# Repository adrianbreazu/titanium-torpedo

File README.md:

# About

IoT Django project for Raspberry Pi 3. It uses a wide range of sensors and actuators. It also provides the PCB schematics for the IoT boards so you can build them yourself.

# PCB design

IoT PCB design can be found in _titanium-torpedo/doc/EaglePCB_ directory. They represent my design (beginner level) any suggestion will be appreciated.

# Hardware needed

1. Raspberry Pi 3 (for better performance)
2. Relay's
3. DS18B20 temperature sensor (used due to accuracy of +/- 0.5)

# Software needed

* Clone this project
* Raspbian-jessie lite

# Installation

1. Cline this project

# Images

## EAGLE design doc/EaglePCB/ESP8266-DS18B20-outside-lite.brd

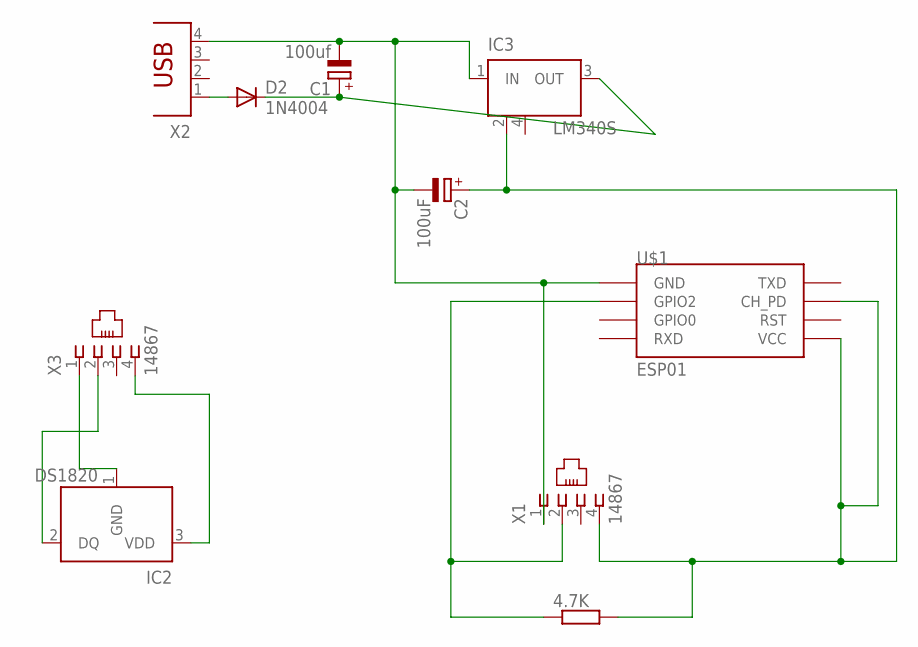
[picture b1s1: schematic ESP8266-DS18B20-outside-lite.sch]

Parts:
4.7K: SMK
C1: 100uf; E2,5-5
C2: 100uF; E2,5-5
D2: 1N4004; DO41-10
IC2: DS1820; TO-92
IC3: LM340S; SOT223
U$1: ESP01
X1, X3: 14867
X2: PN61729

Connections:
3V3: 4.7K.1, C2.+, IC3.2 (GND), U$1.CH_PD, U$1.VCC, X1.4; also elsewhere on the board
5V: C1.+, D2.A, D2.C, IC3.3 (OUT), X2.1
DQ: 4.7K.2, U$1.GPIO2, X1.2; also elsewhere on the board
GND: C1.-, C2.-, IC3.1 (IN), IC3.4 (GND), U$1.GND, X1.1, X2.4
P2_3V3: IC2.3 (VDD), X3.4
P2_DQ: IC2.2 (DQ), X3.2
P2_GND: IC2.1 (GND), X3.1

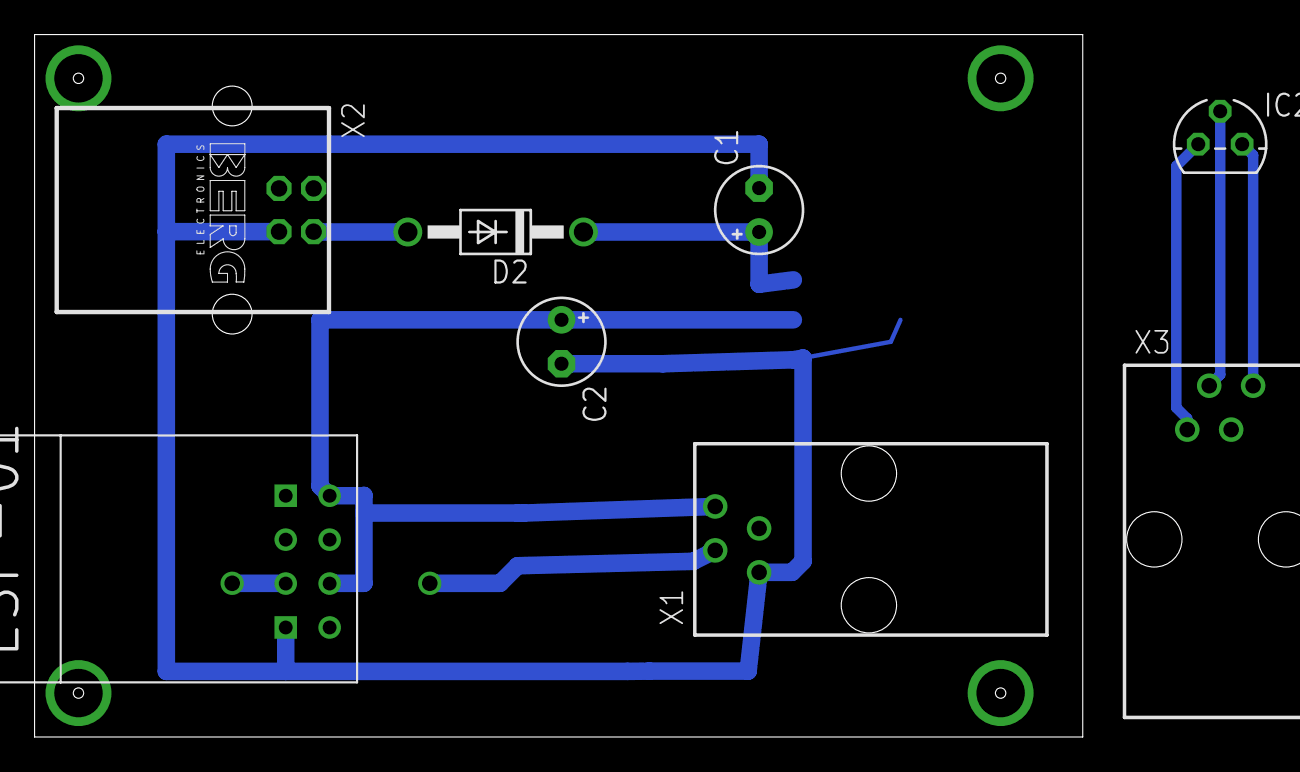
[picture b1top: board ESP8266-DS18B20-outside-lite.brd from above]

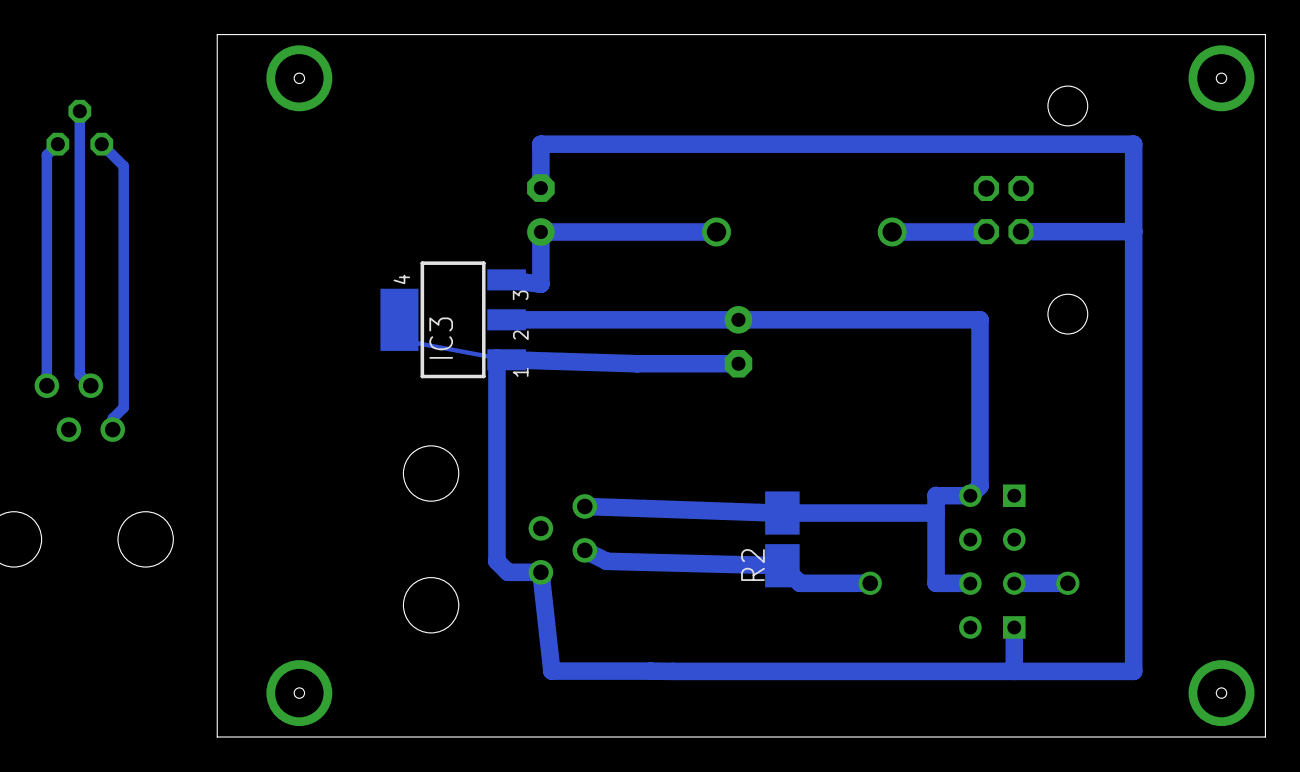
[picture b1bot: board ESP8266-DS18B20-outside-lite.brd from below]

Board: 2 copper layers, 60.6 x 40.6 mm, 10 parts (2 on the bottom side), 7 nets.

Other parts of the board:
R2: SMK

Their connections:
3V3: R2.1; also elsewhere on the board
DQ: R2.2; also elsewhere on the board

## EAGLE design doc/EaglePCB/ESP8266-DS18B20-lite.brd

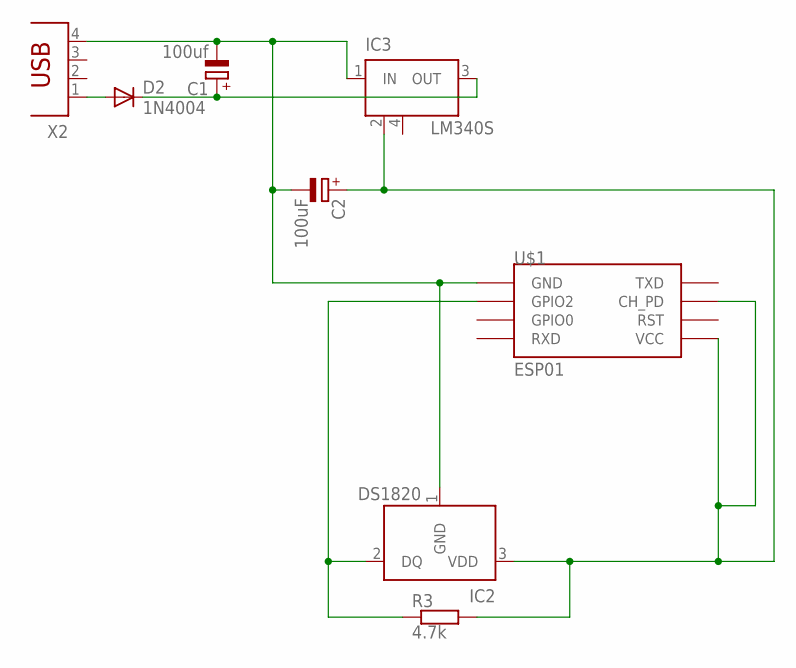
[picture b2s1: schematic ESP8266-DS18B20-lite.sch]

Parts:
C1: 100uf; E2,5-5
C2: 100uF; E2,5-5
D2: 1N4004; DO41-10
IC2: DS1820; TO-92
IC3: LM340S; SOT223
R3: 4.7k; SMK
U$1: ESP01
X2: PN61729

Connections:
3V3: C2.+, IC2.3 (VDD), IC3.2 (GND), R3.1, U$1.CH_PD, U$1.VCC
5V: C1.+, D2.A, D2.C, IC3.3 (OUT), X2.1
DQ: IC2.2 (DQ), R3.2, U$1.GPIO2
GND: C1.-, C2.-, IC2.1 (GND), IC3.1 (IN), IC3.4 (GND), U$1.GND, X2.4

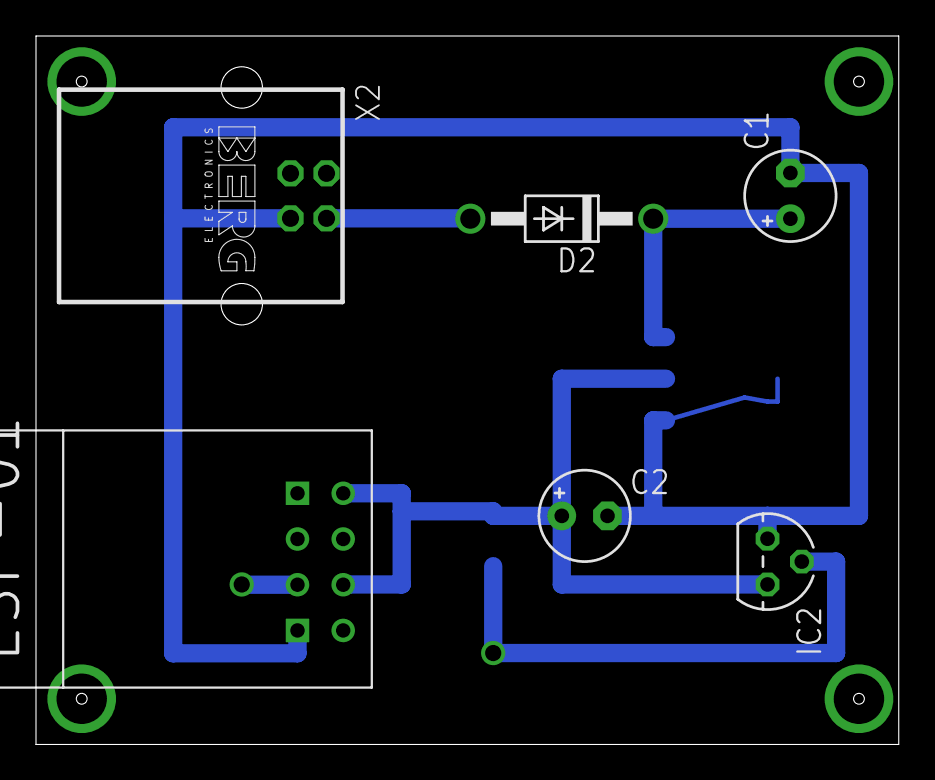
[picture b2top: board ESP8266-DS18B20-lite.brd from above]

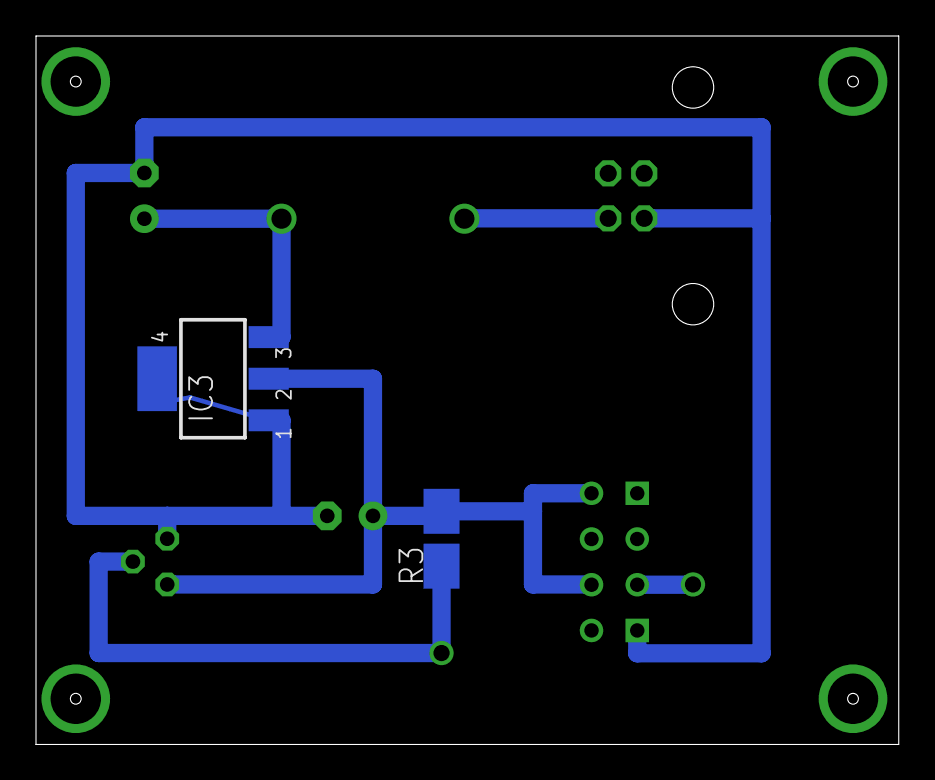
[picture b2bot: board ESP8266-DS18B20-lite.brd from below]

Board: 2 copper layers, 47.9 x 39.4 mm, 8 parts (2 on the bottom side), 4 nets.

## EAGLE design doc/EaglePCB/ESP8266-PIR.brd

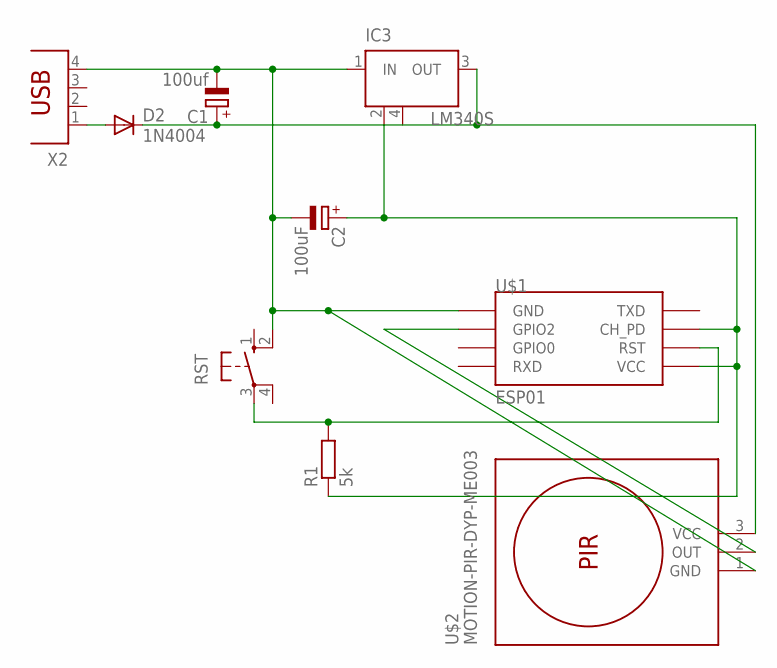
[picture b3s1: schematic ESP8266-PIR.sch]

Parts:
C1: 100uf; E2,5-5
C2: 100uF; E2,5-5
D2: 1N4004; DO41-10
IC3: LM340S; SOT223
R1: 5k; 0204/7
RST: 10-XX; B3F-10XX
U$1: ESP01
U$2: MOTION-PIR-DYP-ME003
X2: PN61729

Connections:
3V3: C2.+, IC3.2 (GND), R1.1, U$1.CH_PD, U$1.VCC
5V: C1.+, D2.A, D2.C, IC3.3 (OUT), U$2.3 (VCC), X2.1
GND: C1.-, C2.-, IC3.1 (IN), IC3.4 (GND), RST.2 (S1), U$1.GND, U$2.1 (GND), X2.4
GPIO2: U$1.GPIO2, U$2.2 (OUT)
unnamed: R1.2, RST.3, U$1.RST

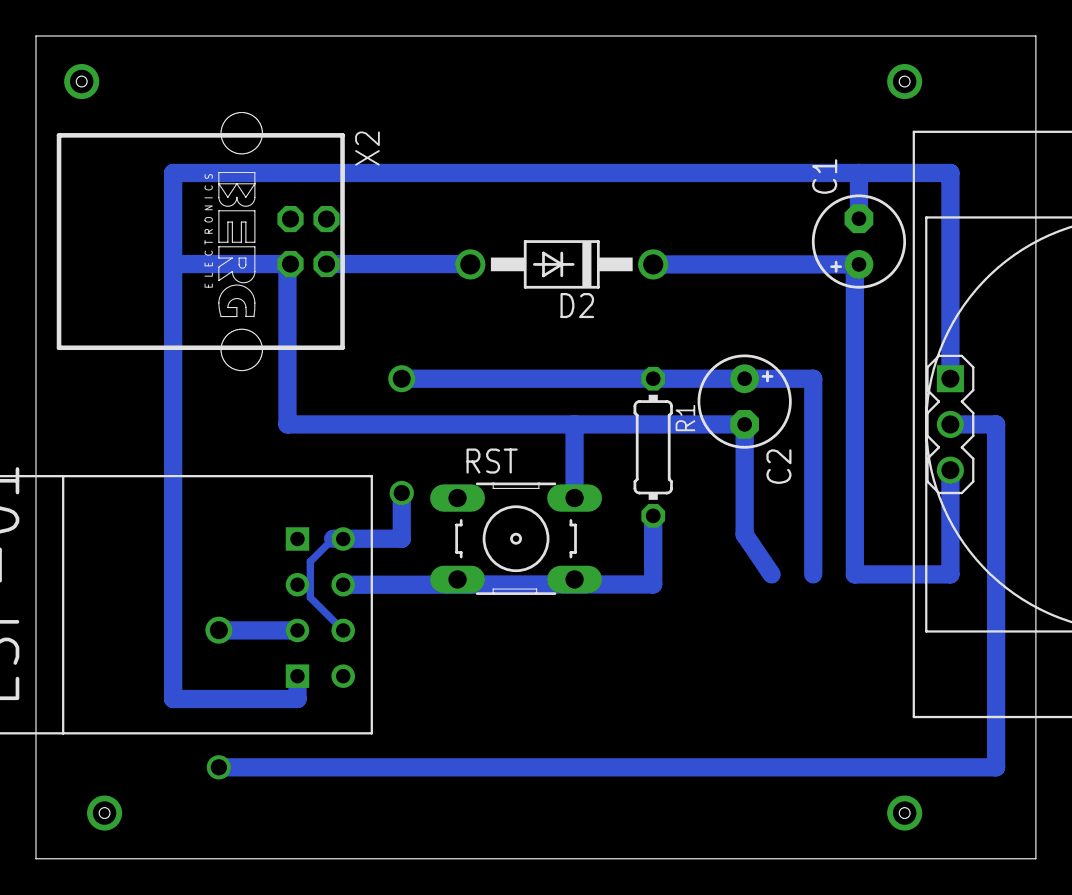
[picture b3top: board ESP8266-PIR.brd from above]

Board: 2 copper layers, 55.5 x 45.7 mm, 9 parts (1 on the bottom side), 5 nets.

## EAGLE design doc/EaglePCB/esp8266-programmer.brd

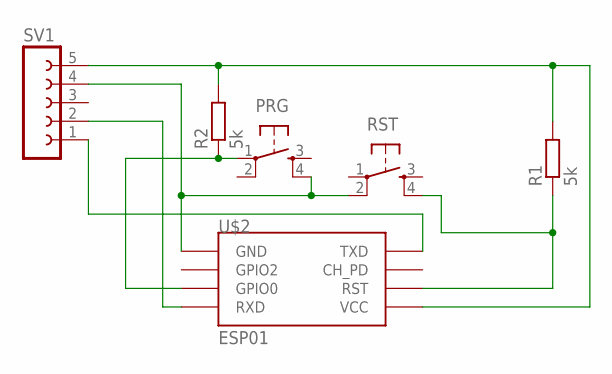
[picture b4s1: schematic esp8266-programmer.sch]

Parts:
PRG: TAC_SWITCHPTH; TACTILE-PTH
R1, R2: 5k; 0207/10
RST: TAC_SWITCHPTH; TACTILE-PTH
SV1: FE05W
U$2: ESP01

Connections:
3V3: R1.2, R2.2, SV1.5, U$2.VCC
GND: PRG.4, RST.2, SV1.4, U$2.GND
GPIO0: PRG.1, R2.1, U$2.GPIO0
RST: R1.1, RST.4, U$2.RST
RX-TX: SV1.1, U$2.TX (TXD)
TX-RX: SV1.2, U$2.RX (RXD)

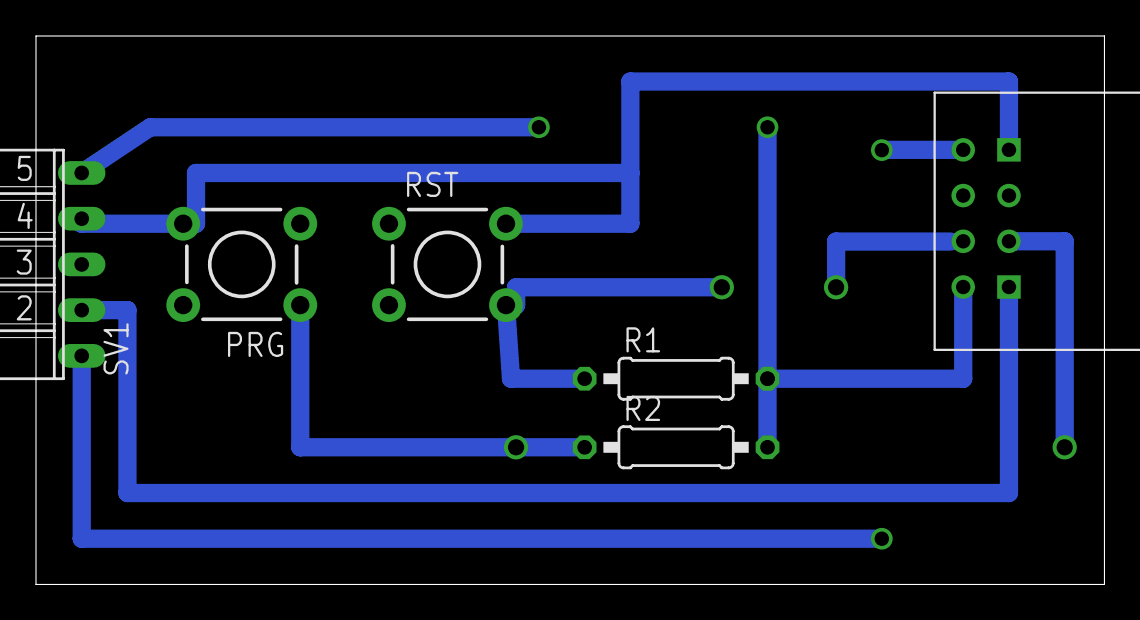
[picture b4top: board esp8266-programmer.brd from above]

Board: 2 copper layers, 59.4 x 30.5 mm, 6 parts (0 on the bottom side), 6 nets.

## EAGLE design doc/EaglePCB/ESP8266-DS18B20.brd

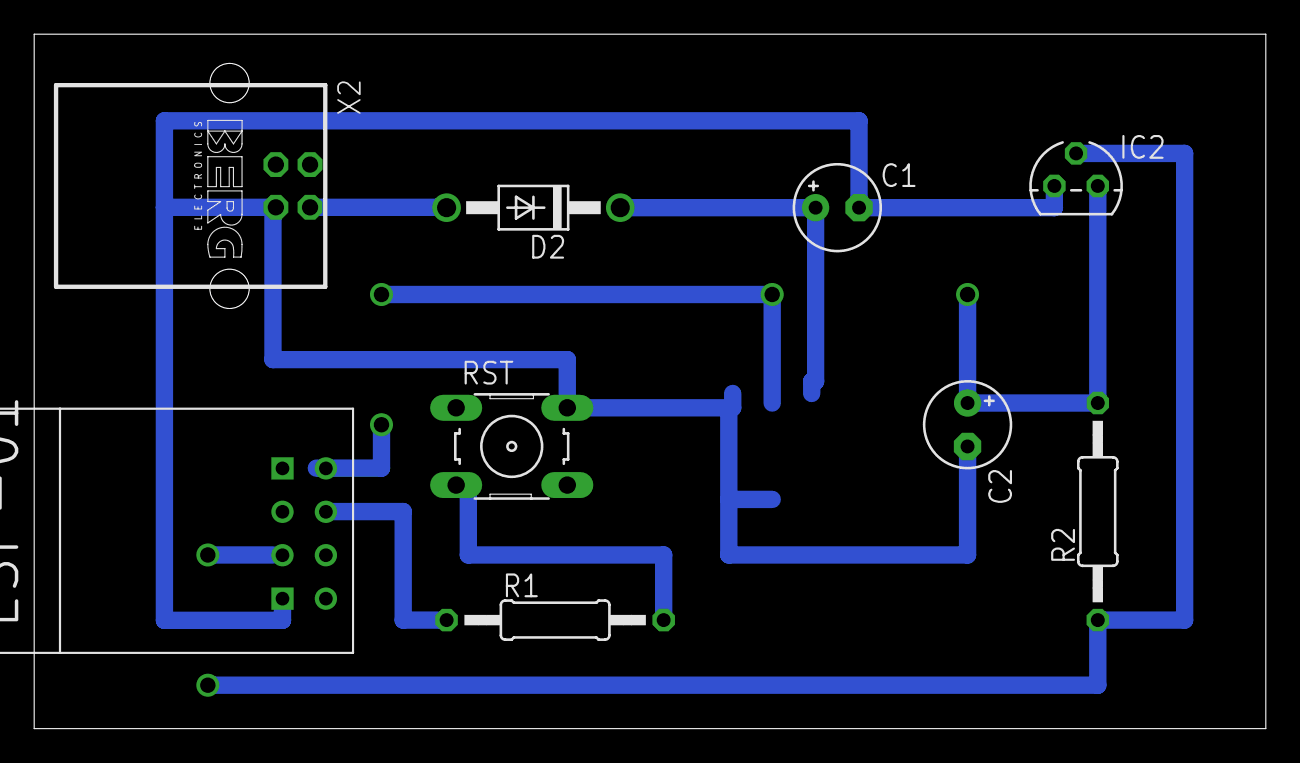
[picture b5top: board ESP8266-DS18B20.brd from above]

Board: 2 copper layers, 72.1 x 40.6 mm, 10 parts (1 on the bottom side), 6 nets.

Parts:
C1: 100uf; E2,5-5
C2: 100uF; E2,5-5
D2: 1N4004; DO41-10
IC2: DS1820; TO-92
IC3: LM340S; SOT223
R1: 1k; 0207/12
R2: 4.7k; 0207/12
RST: B3F-10XX
U$1: ESP01
X2: PN61729

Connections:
3V3: C2.+, IC2.3, IC3.2, R2.2, U$1.CH_PD, U$1.VCC
5V: C1.+, D2.A, D2.C, IC3.3, X2.1
DQ: IC2.2, R2.1, U$1.GPIO2
GND: C1.-, C2.-, IC2.1, IC3.1, IC3.4, RST.2, U$1.GND, X2.4
GND(RST): R1.2, RST.3
RST: R1.1, U$1.RST

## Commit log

2016-12-23 add idea folder to ignore list
2016-12-23 create django project
2016-12-23 add gentelella bootsratp to the project
2016-12-23 change timezone and add templates to settings.py
2016-12-23 add admin with administrator as superuser
2016-12-24 create sensors_actuators app followed and basic configure of urls.py files
2016-12-25 initial commit of PCB design
2016-12-25 update README.md file
2016-12-25 add DS18B20 temperature page response Arduino file
2016-12-26 add ds18b20 JSON response Arduino code
2016-12-31 add font awesome
2016-12-31 initial base and index html pages
2017-01-01 add 404 page, updated base, initial model and ds18b20 POST request handler
2017-01-02 update ESP8266 IoT with ds18b20, so it will send json data to django app
2017-01-03 small fixes
2017-01-04 add venv
2017-01-05 correct PCB design and add PIR IoT device
2017-01-06 prepare for vector watch stream
2017-01-06 small fix to the getLastData
2017-01-07 add initial vector code
2017-01-07 vector small fixes
2017-01-07 initial dashboard view
2017-01-07 add table view
2017-01-22 add lite version of ds18b20 board and one with an external RJ11 connector
2017-08-04 add clujbike support
2017-08-04 add chart
2017-08-10 add js chart filter
2017-08-10 add new data
2018-05-01 bulk 1 of changes
2018-12-31 cleanup, new dashboard, changed left-side bar and new actuator
2018-12-31 cleanup
2019-01-01 add notification support for sensor errors (in case they send nothing in the last hour)
2019-01-01 small fix notifications
2019-01-02 actuators cleanup
2019-01-03 enhance dashborad view with sensor data
2019-01-13 add logging to view.py
2019-06-02 add scheduler support and cron support
2019-06-09 remove comment
2019-06-12 add pushbullet supper and environment.json for easy deploment
2019-07-02 fix cron job and add pushbullet notification for missing sensor data
2019-10-30 Bump django from 1.10.4 to 1.11.23
    Bumps [django](https://github.com/django/django) from 1.10.4 to 1.11.23.
    - [Release notes](https://github.com/django/django/releases)
    - [Commits](https://github.com/django/django/compare/1.10.4...1.11.23)
2020-02-11 Bump django from 1.10.4 to 1.11.28
    Bumps [django](https://github.com/django/django) from 1.10.4 to 1.11.28.
    - [Release notes](https://github.com/django/django/releases)
    - [Commits](https://github.com/django/django/compare/1.10.4...1.11.28)
2020-06-05 Bump django from 1.10.4 to 1.11.29
    Bumps [django](https://github.com/django/django) from 1.10.4 to 1.11.29.
    - [Release notes](https://github.com/django/django/releases)
    - [Commits](https://github.com/django/django/compare/1.10.4...1.11.29)
2021-06-10 Bump django from 1.10.4 to 2.2.24
    Bumps [django](https://github.com/django/django) from 1.10.4 to 2.2.24.
    - [Release notes](https://github.com/django/django/releases)
    - [Commits](https://github.com/django/django/compare/1.10.4...2.2.24)
    ---
    updated-dependencies:
    - dependency-name: django
2023-07-18 Bump django from 1.10.4 to 2.2.28
    Bumps [django](https://github.com/django/django) from 1.10.4 to 2.2.28.
    - [Commits](https://github.com/django/django/compare/1.10.4...2.2.28)
    ---
    updated-dependencies:
    - dependency-name: django
    dependency-type: direct:production

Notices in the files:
parts and their libraries:
diy-modules: Released under the Creative Commons Attribution 4.0 International License: http://creativecommons.org/licenses/by/4.0
SparkFun-Retired: Licensing:Creative Commons ShareAlike 4.0 International - https://creativecommons.org/licenses/by-sa/4.0
